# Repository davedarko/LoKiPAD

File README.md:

# LoKiPAD
A low cost adafruit [macropad](https://learn.adafruit.com/adafruit-macropad-rp2040/) clone with integrated todbot [MacroPadSynthPlug!](https://github.com/todbot/macropadsynthplug) Partslist is kept minimal and some things like the SD-card adapter, debug LED and speaker were dropped. Generic 12mm SMD buttons, 3535 WS2812B LEDs, an OLED module and a Raspberry PI Pico keep the price low. Check the ibom file for more info on the resistor and capacitor values. There's a small hack necessary so you don't have to remove the PCB from the case to push the BOOTSEL button - connect the pad with a jumper wire to a pin of the pico bootsel button.

## Code
Chose the Adafruit MacroPad RP2040 to compile the Arduino examples from todbot, so the SPI pins for the display are setup correctly. You also have to (re)define some pins to make the oled display and the LEDs work. There might be an issue with the encoder - if it feels backwards, just swap the PIN_ROTA and PIN_ROTB definition.

Since this is hardware to run todbots code, there's no code of my own to find here.

```c
#define PIN_NEOPIXEL 19
#define PIN_ROTA 18
#define PIN_ROTB 17
#define OLED_DC  14
#define OLED_RST 15
#define OLED_CS  22
```
## code of other people
This [MIDI controller code](https://gist.github.com/codeandmake/a2a5672fd49b748823cb352ba72d804a) by @codeandmake works great too, once you've changed the pin definition. 
---

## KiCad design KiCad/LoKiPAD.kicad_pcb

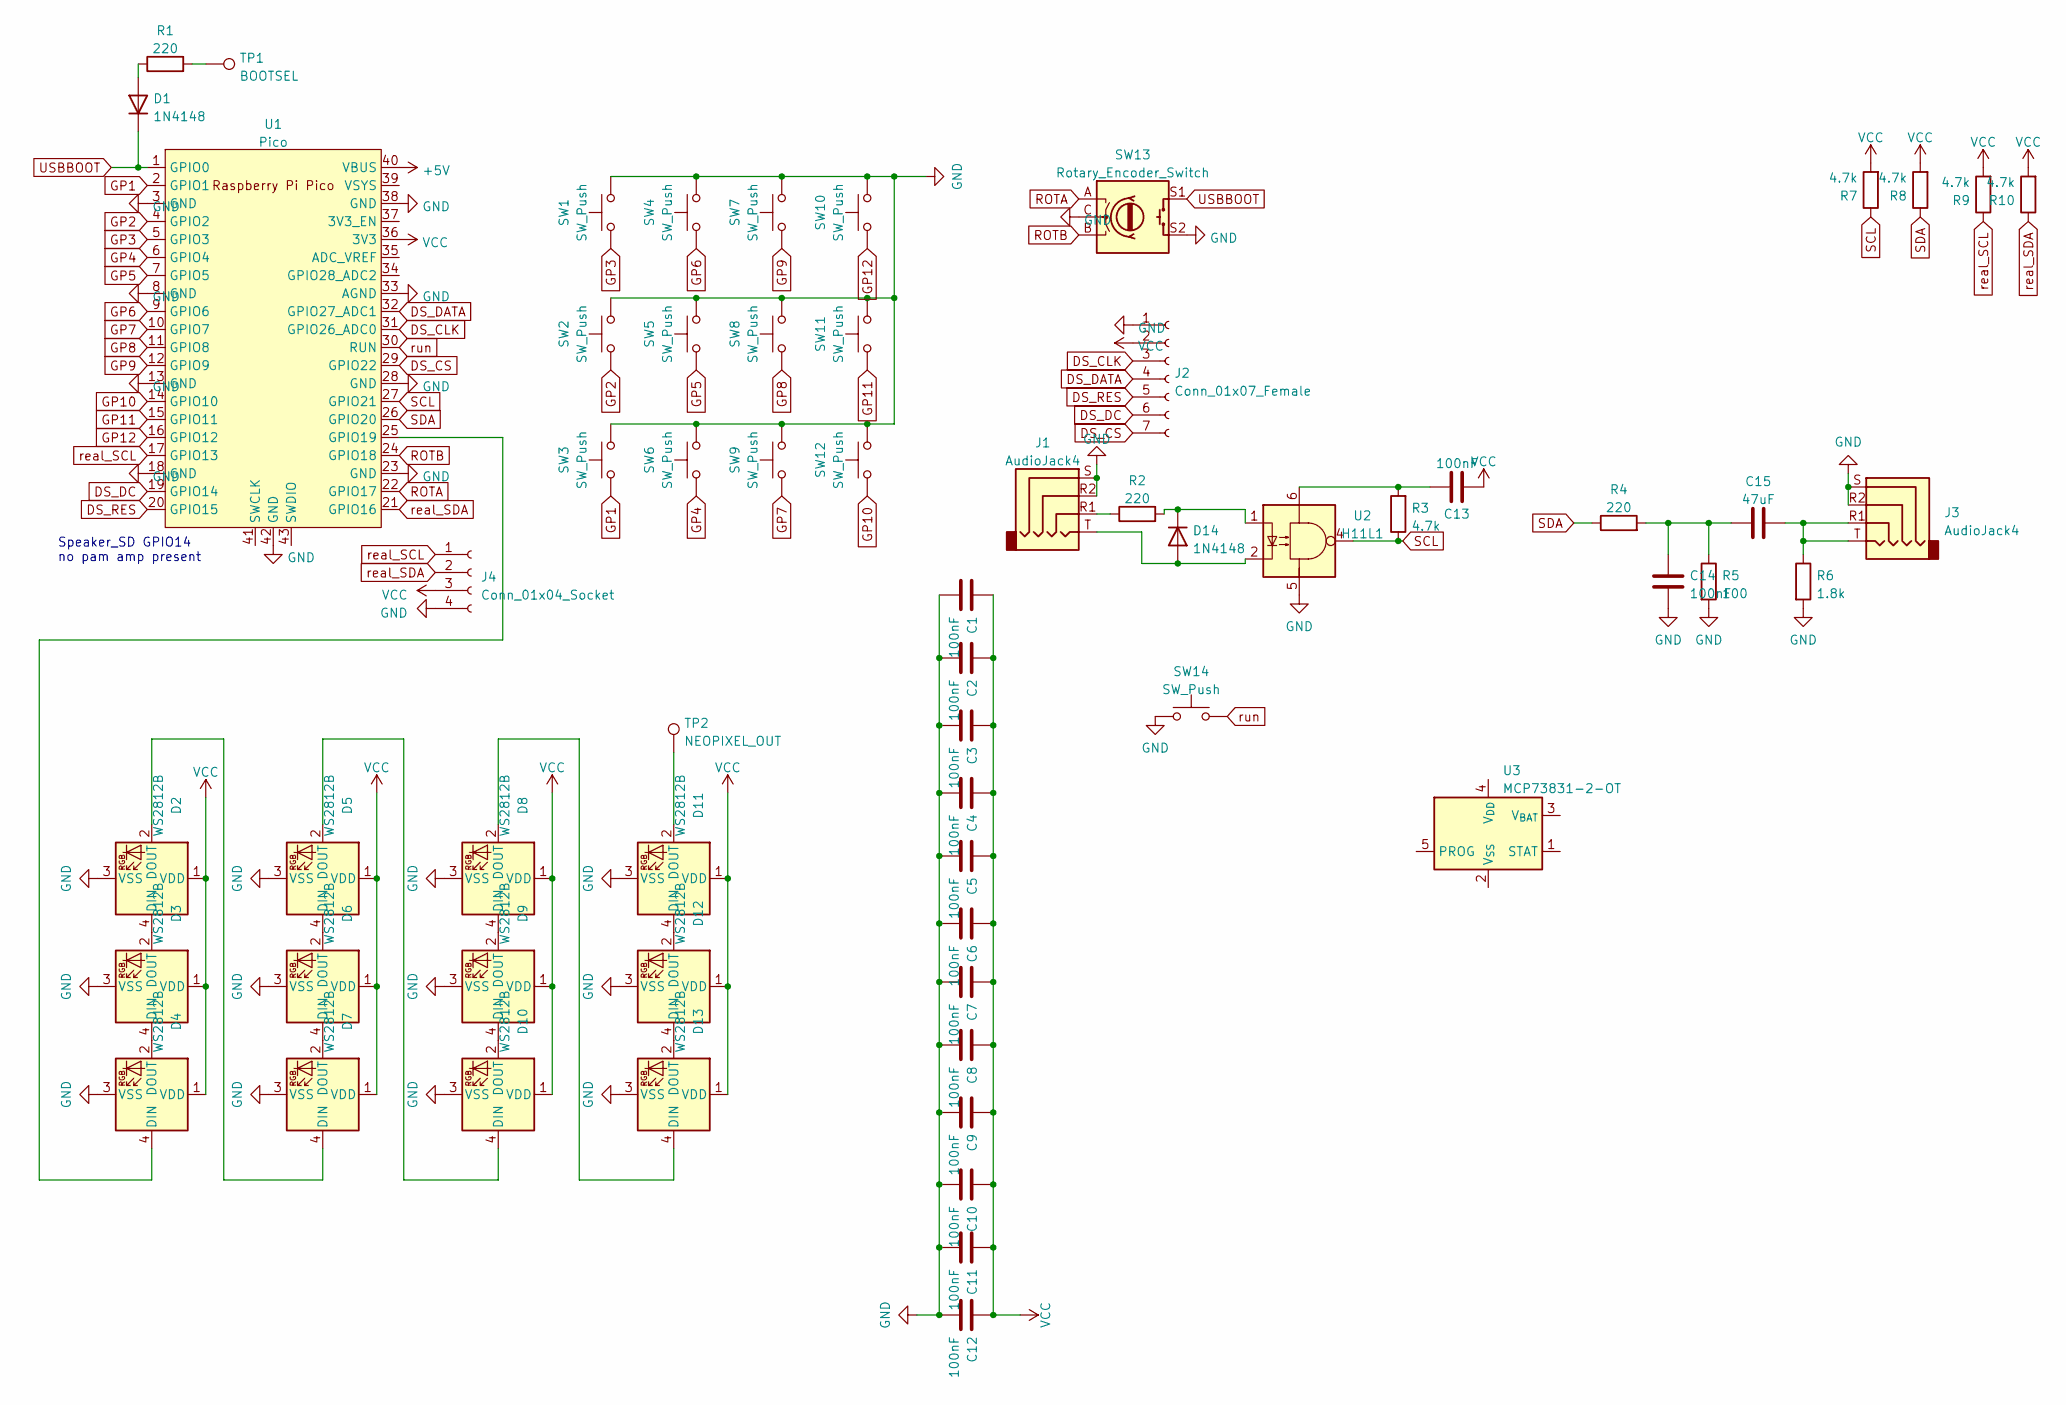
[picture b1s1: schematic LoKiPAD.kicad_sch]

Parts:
C1, C2, C3, C4, C5, C6, C7, C8, C9, C10, C11, C12, C13, C14: 100nF; C_0603_1608Metric_Pad1.08x0.95mm_HandSolder
C15: 47uF; C_0603_1608Metric_Pad1.08x0.95mm_HandSolder
D1, D14: 1N4148; D_0805_2012Metric_Pad1.15x1.40mm_HandSolder
D2, D3, D4, D5, D6, D7, D8, D9, D10, D11, D12, D13: WS2812B; LED_SK6812MINI_PLCC4_3.5x3.5mm_P1.75mm
J1, J3: AudioJack4; Jack_3.5mm_PJ320D_Horizontal
J2: Conn_01x07_Female; PinHeader_1x07_P2.54mm_Vertical
J4: Conn_01x04_Socket; JST_SH_BM04B-SRSS-TB_1x04-1MP_P1.00mm_Vertical
R1, R2, R4: 220; R_0603_1608Metric_Pad0.98x0.95mm_HandSolder
R3, R7, R8, R9, R10: 4.7k; R_0603_1608Metric_Pad0.98x0.95mm_HandSolder
R5: 100; R_0603_1608Metric_Pad0.98x0.95mm_HandSolder
R6: 1.8k; R_0603_1608Metric_Pad0.98x0.95mm_HandSolder
SW1, SW2, SW3, SW4, SW5, SW6, SW7, SW8, SW9, SW10, SW11, SW12: SW_Push; SW_PUSH-12mm-SMD
SW13: Rotary_Encoder_Switch; RotaryEncoder_Alps_EC11E-Switch_Vertical_H20mm_CircularMoun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
SW14: SW_Push; SW_Push_1P1T_NO_CK_KMR2
TP1: BOOTSEL; TestPoint_Pad_D1.5mm
TP2: NEOPIXEL_OUT; TestPoint_Pad_D1.5mm
U1: Pico; RPi_Pico_SMD
U2: H11L1; DIP-6_W8.89mm_SMDSocket_LongPads
U3: MCP73831-2-OT; SOT-23-5

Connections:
+5V: U1.40 (VBUS)
DS_CLK: J2.3, U1.31 (GPIO26_ADC0)
DS_CS: J2.7, U1.29 (GPIO22)
DS_DATA: J2.4, U1.32 (GPIO27_ADC1)
DS_DC: J2.6, U1.19 (GPIO14)
DS_RES: J2.5, U1.20 (GPIO15)
GND: C1.2, C2.2, C3.2, C4.2, C5.2, C6.2, C7.2, C8.2, C9.2, C10.2, C11.2, C12.2, C14.2, D2.3 (VSS), D3.3 (VSS), D4.3 (VSS), D5.3 (VSS), D6.3 (VSS), D7.3 (VSS), D8.3 (VSS), D9.3 (VSS), D10.3 (VSS), D11.3 (VSS), D12.3 (VSS), D13.3 (VSS), J1.R2, J1.S, J2.1, J3.R2, J3.S, J4.4, R5.2, R6.2, SW1.2, SW2.2, SW3.2, SW4.2, SW5.2, SW6.2, SW7.2, SW8.2, SW9.2, SW10.2, SW11.2, SW12.2, SW13.C, SW13.S2, SW14.1, U1.3 (GND), U1.8 (GND), U1.13 (GND), U1.18 (GND), U1.23 (GND), U1.28 (GND), U1.33 (AGND), U1.38 (GND), U1.42 (GND), U2.5
GP1: SW3.1, U1.2 (GPIO1)
GP2: SW2.1, U1.4 (GPIO2)
GP3: SW1.1, U1.5 (GPIO3)
GP4: SW6.1, U1.6 (GPIO4)
GP5: SW5.1, U1.7 (GPIO5)
GP6: SW4.1, U1.9 (GPIO6)
GP7: SW9.1, U1.10 (GPIO7)
GP8: SW8.1, U1.11 (GPIO8)
GP9: SW7.1, U1.12 (GPIO9)
GP10: SW12.1, U1.14 (GPIO10)
GP11: SW11.1, U1.15 (GPIO11)
GP12: SW10.1, U1.16 (GPIO12)
unnamed: C13.1, R3.2, U2.6
unnamed: C14.1, C15.1, R4.2, R5.1
unnamed: C15.2, J3.R1, J3.T, R6.1
unnamed: D1.2 (A), R1.1
unnamed: D2.4 (DIN), D3.2 (DOUT)
unnamed: D2.2 (DOUT), D7.4 (DIN)
unnamed: D3.4 (DIN), D4.2 (DOUT)
unnamed: D4.4 (DIN), U1.25 (GPIO19)
unnamed: D5.4 (DIN), D6.2 (DOUT)
unnamed: D6.4 (DIN), D7.2 (DOUT)
unnamed: D8.4 (DIN), D9.2 (DOUT)
unnamed: D5.2 (DOUT), D10.4 (DIN)
unnamed: D9.4 (DIN), D10.2 (DOUT)
unnamed: D11.4 (DIN), D12.2 (DOUT)
unnamed: D11.2 (DOUT), TP2.1
unnamed: D12.4 (DIN), D13.2 (DOUT)
unnamed: D8.2 (DOUT), D13.4 (DIN)
unnamed: D14.2 (A), J1.T, U2.2
unnamed: D14.1 (K), R2.2, U2.1
unnamed: J1.R1, R2.1
unnamed: R1.2, TP1.1
ROTA: SW13.A, U1.22 (GPIO17)
ROTB: SW13.B, U1.24 (GPIO18)
SCL: R3.1, R7.1, U1.27 (GPIO21), U2.4
SDA: R4.1, R8.1, U1.26 (GPIO20)
USBBOOT: D1.1 (K), SW13.S1, U1.1 (GPIO0)
VCC: C1.1, C2.1, C3.1, C4.1, C5.1, C6.1, C7.1, C8.1, C9.1, C10.1, C11.1, C12.1, C13.2, D2.1 (VDD), D3.1 (VDD), D4.1 (VDD), D5.1 (VDD), D6.1 (VDD), D7.1 (VDD), D8.1 (VDD), D9.1 (VDD), D10.1 (VDD), D11.1 (VDD), D12.1 (VDD), D13.1 (VDD), J2.2, J4.3, R7.2, R8.2, R9.2, R10.2, U1.36 (3V3)
real_SCL: J4.1, R9.1, U1.17 (GPIO13)
real_SDA: J4.2, R10.1, U1.21 (GPIO16)
run: SW14.2, U1.30 (RUN)

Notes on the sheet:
Speaker_SD GPIO14 no pam amp present

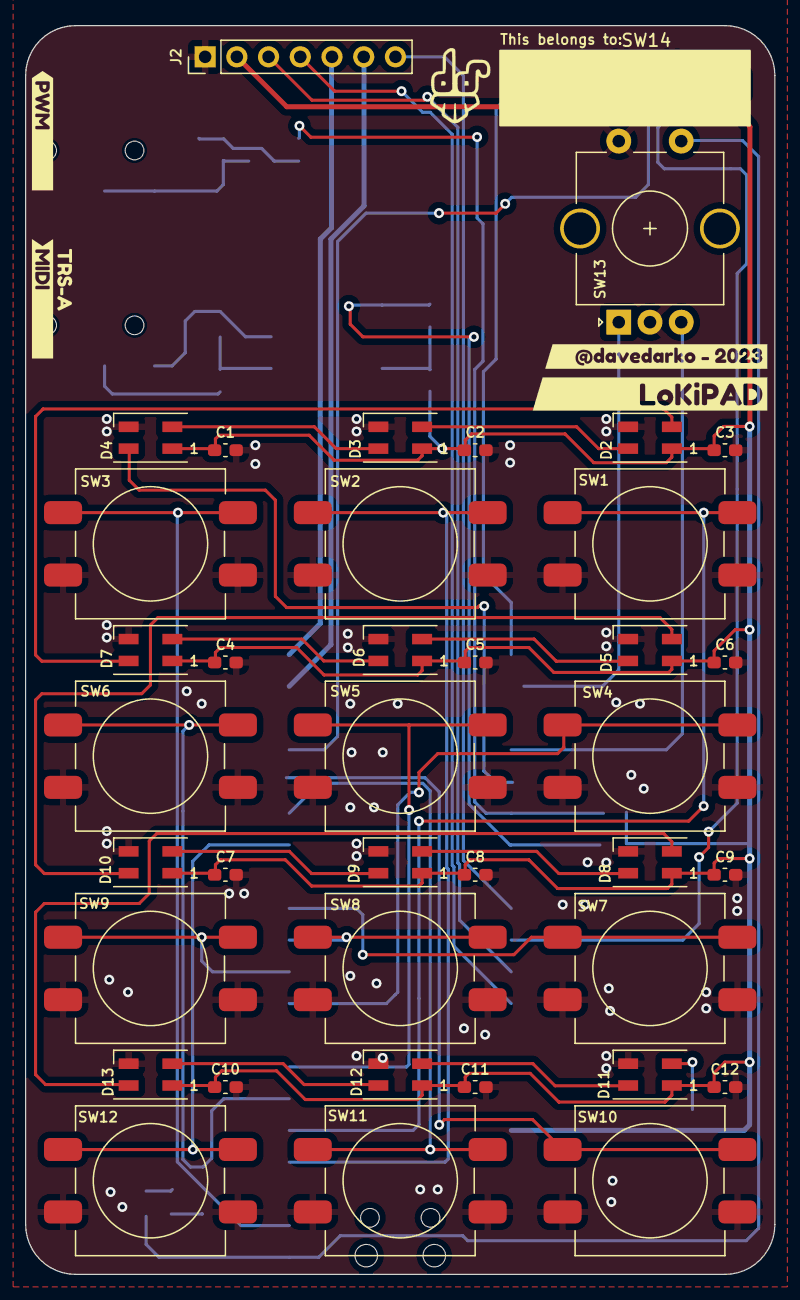
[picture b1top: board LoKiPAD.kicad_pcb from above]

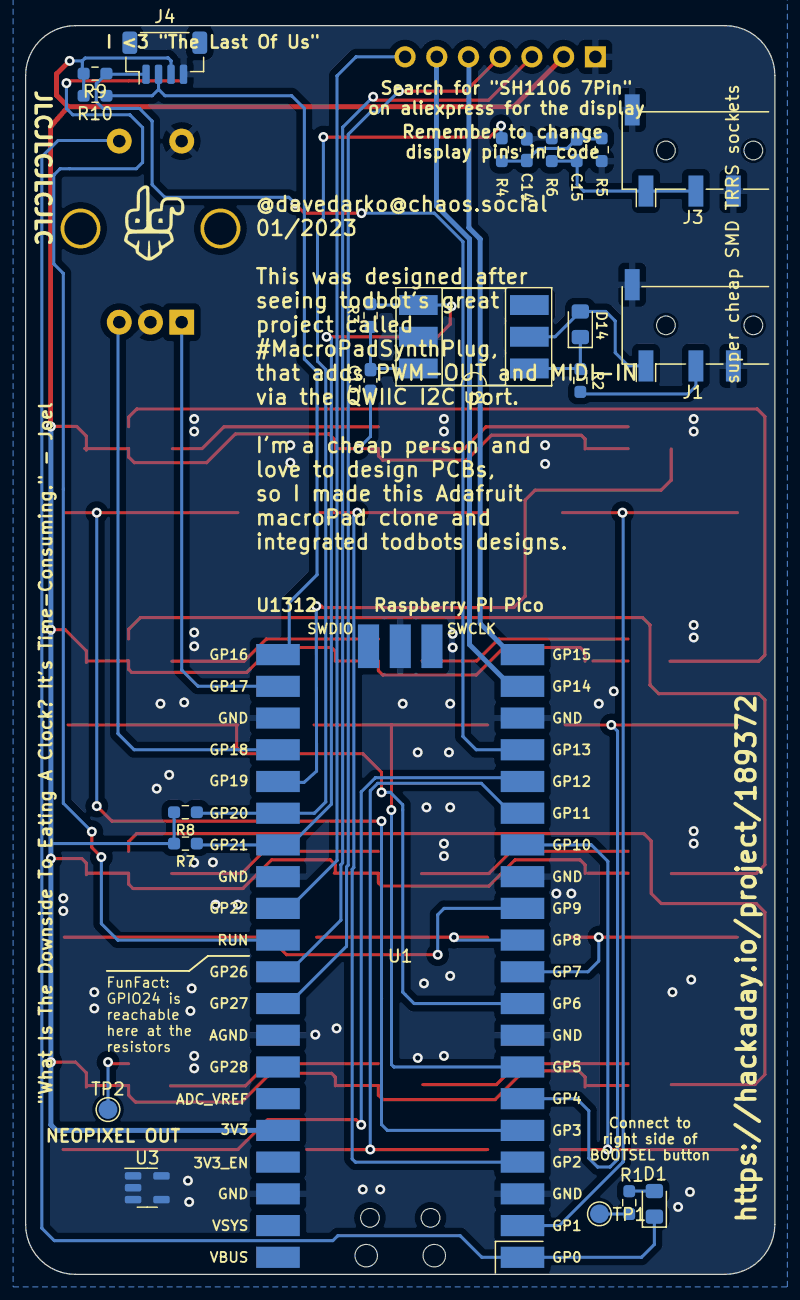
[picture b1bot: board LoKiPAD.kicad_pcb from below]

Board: 2 copper layers, 60.0 x 100.0 mm, 69 parts (24 on the bottom side), 48 nets.

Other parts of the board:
Ref**: Val**; davedarko_logo_silk_outline
Ref**#2: Val**; davedarko_logo_silk_outline
kibuzzard-63D6CFE9: G***; kibuzzard-63D6CFE9
kibuzzard-63D676B5: G***; kibuzzard-63D676B5
kibuzzard-63D67702: G***; kibuzzard-63D67702
kibuzzard-63D67711: G***; kibuzzard-63D67711
kibuzzard-63E7EF8E: G***; kibuzzard-63E7EF8E

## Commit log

2023-02-12 pcbs design files and case
2023-02-12 documentation
2023-02-12 added rounded box file
2023-02-22 schematics pdf
2023-04-14 bigger cutout for pico
2023-04-14 more parts moved to back, kicad7
2023-04-14 backup of updated first version
